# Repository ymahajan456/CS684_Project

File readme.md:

Project Name: Hexapod Navigation With WiFi RRSI

Team Members:
1. Meet Udeshi    : 14D070007
2. Prathu Baronia : 14D070046
3. Yogesh Mahajan : 14D070022

Project Description:
The most important objective of this project is to implement an efficient and reliable WiFi
RSSI based localization system and use it to navigate the hexapod in designated area.
Previous implementations have shown that RSSI could give accuracy up to 10 cm in 2m×2m
area. This decides the size of test area.

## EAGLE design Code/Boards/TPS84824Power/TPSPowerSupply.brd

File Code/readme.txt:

2018 - CS684  Group 5 : Hexapod Navigtaion 
================================================ 
 
Group Info: 
------------ 
1. Meet Udeshi    : 14D070007
2. Prathu Baronia : 14D070046
3. Yogesh Mahajan : 14D070022
 
Extension Of 
------------ 
Archrobotic's Hexy : Open Source Low Cost Arduino DIY Hexapood Kit 

Project Description 
------------------- 
The objective of this project is to implement an efficient and reliable WiFi
RSSI based localization system and use it to navigate the hexapod in designated area.
Previous implementations have shown that RSSI could give accuracy up to 10 cm in 2m×2m
area. This decides the size of test area.
 
Technologies Used 
------------------- 
 
Remove the items that do no apply to your project and keep the remaining ones. 
 
+   Xbee 
+   Python 
+   Specialized Hardware 

emonstration Video 
=========================  
[Demo 1]{https://youtu.be/1PUA8-5pAxc}
[Demo 2]{https://youtu.be/FjIFfGolqqk}

References 
=========== 
 
[Development of a portable XBee C library and RSSI triangulation localization framework]{https://ieeexplore.ieee.org/document/7029375/}
[Utilization of XBee ZigBee modules and MATLAB for RSSI localization applications]{https://ieeexplore.ieee.org/document/7925305/}
[Archrobotic's Git Repository]{https://github.com/arcbotics/hexy}
[Getting started with Hexy]{http://arcbotics.com/products/hexy/start/building-your-hexy-the-hexapod/}
[Archrobotic's controller]{http://arcbotics.com/lessons/using-pomoco-2-0/}

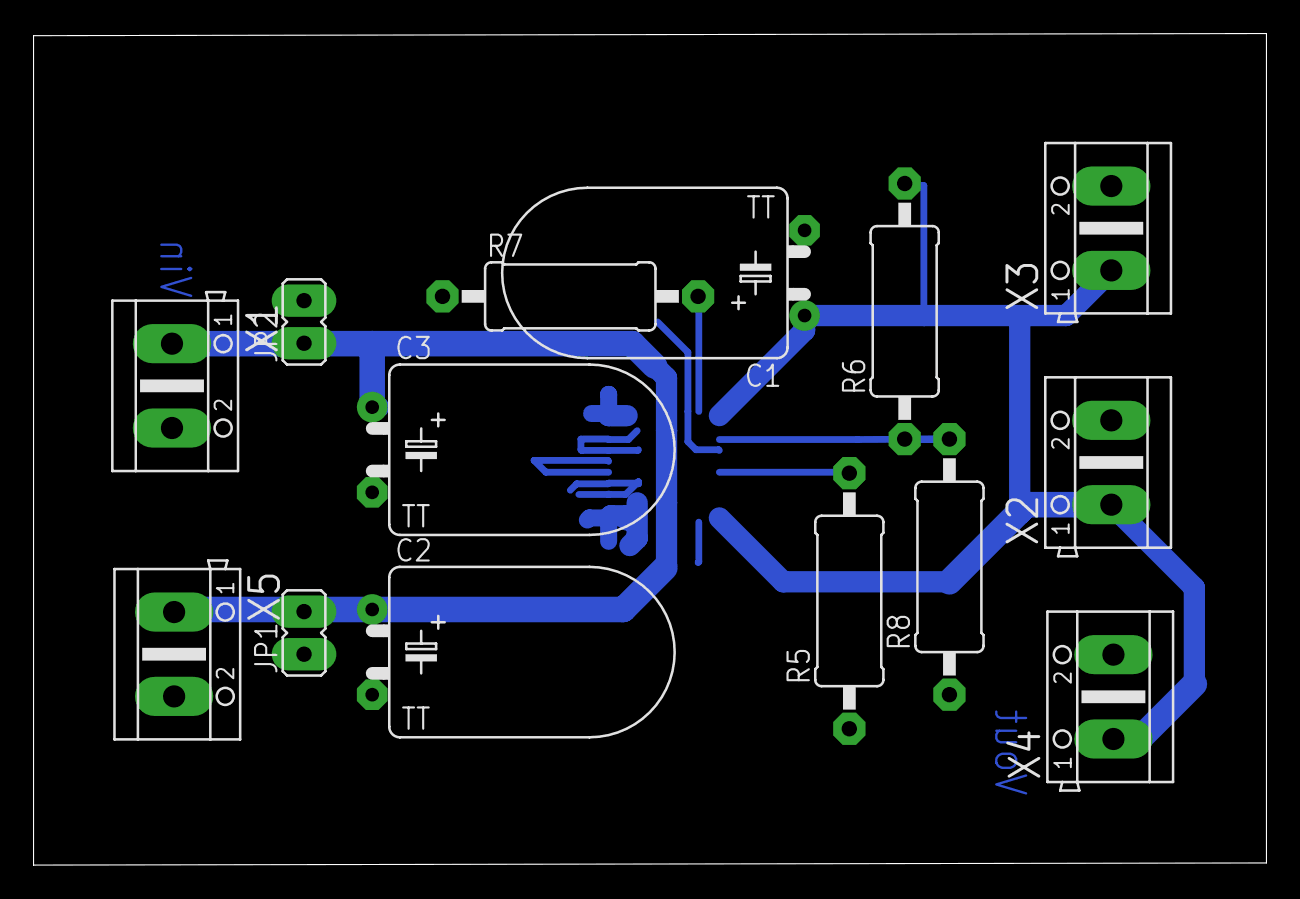
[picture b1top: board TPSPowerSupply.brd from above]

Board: 2 copper layers, 73.5 x 49.6 mm, 15 parts (1 on the bottom side), 7 nets.

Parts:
C1: 100u; TT5D11L
C2, C3: 10u; TT5D11L
JP1, JP2: JP1
R5: 11k; 0411/15
R6: 10k; 0411/15
R7: 40.2k; 0411/15
R8: 1.37k; 0411/15
U1: Value; MOL0024A
X1, X2, X3, X4, X5: AK500/2

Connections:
GND: C1.-, C2.-, C3.-, R5.1, R7.1, R8.1, U1.3, U1.9, U1.12, U1.13, U1.14, U1.15, U1.18, U1.19, U1.20, U1.21, U1.23, X1.2, X2.2, X3.2, X4.2, X5.2
unnamed: R6.1, R8.2, U1.2
unnamed: R7.2, U1.24
unnamed: R5.2, U1.5
unnamed: U1.16, U1.17
VIN: C2.+, C3.+, JP1.1, JP1.2, JP2.1, JP2.2, U1.11, U1.22, X1.1, X5.1
VOUT: C1.+, R6.2, U1.1, U1.8, X2.1, X3.1, X4.1

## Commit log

2018-04-29 Project Documentation Complete
2018-04-29 Power supply board added
2018-04-29 Hexy STD files added
